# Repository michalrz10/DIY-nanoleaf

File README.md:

# DIY nanoleaf
## Programmed functionality
 - Turn on/off leds
 - Turn on/off build in led
 - Single color
 - Random color on each segment every 5 seconds
 - Single random color every 5 seconds
 - Smooth change on each segment color
 - Smooth change of single color
 - Smooth change of pairs of segments
 - Api to control each segment color. For exaplle changing color with music described in <a href="Pythonn App">Python app</a>  

  Blue eye  
     
  Music Api  
    
## Ways to controll
 - Website
 - <a href="Python App">Windows app</a>
 - <a href="Android App">Android app</a>
## Case
All the <a href="3D model">parts</a> were 3D printed with pla and connected with 1 cm spacers.  
 
There is a reflective material glued on the back of the case.  
Cover was printed in 2 layers of translusend pla. Later I glued thin paper to cover so the light was more diffused.  
   
## Electronics
### Used:
 - Esp32 to controll leds
 - 5m RGB Led strip 12V devided in 10 segments for each hexagon
 - 15 N-Mosfets to controll 5 different colors through Esp32
 - Led power suppy
 - Mini 360 DC-DC step-down converter
  
### Diagram

### <a href="Board project">Board</a>

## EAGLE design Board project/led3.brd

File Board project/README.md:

# Board  
Board Diagram  
  
Generated board

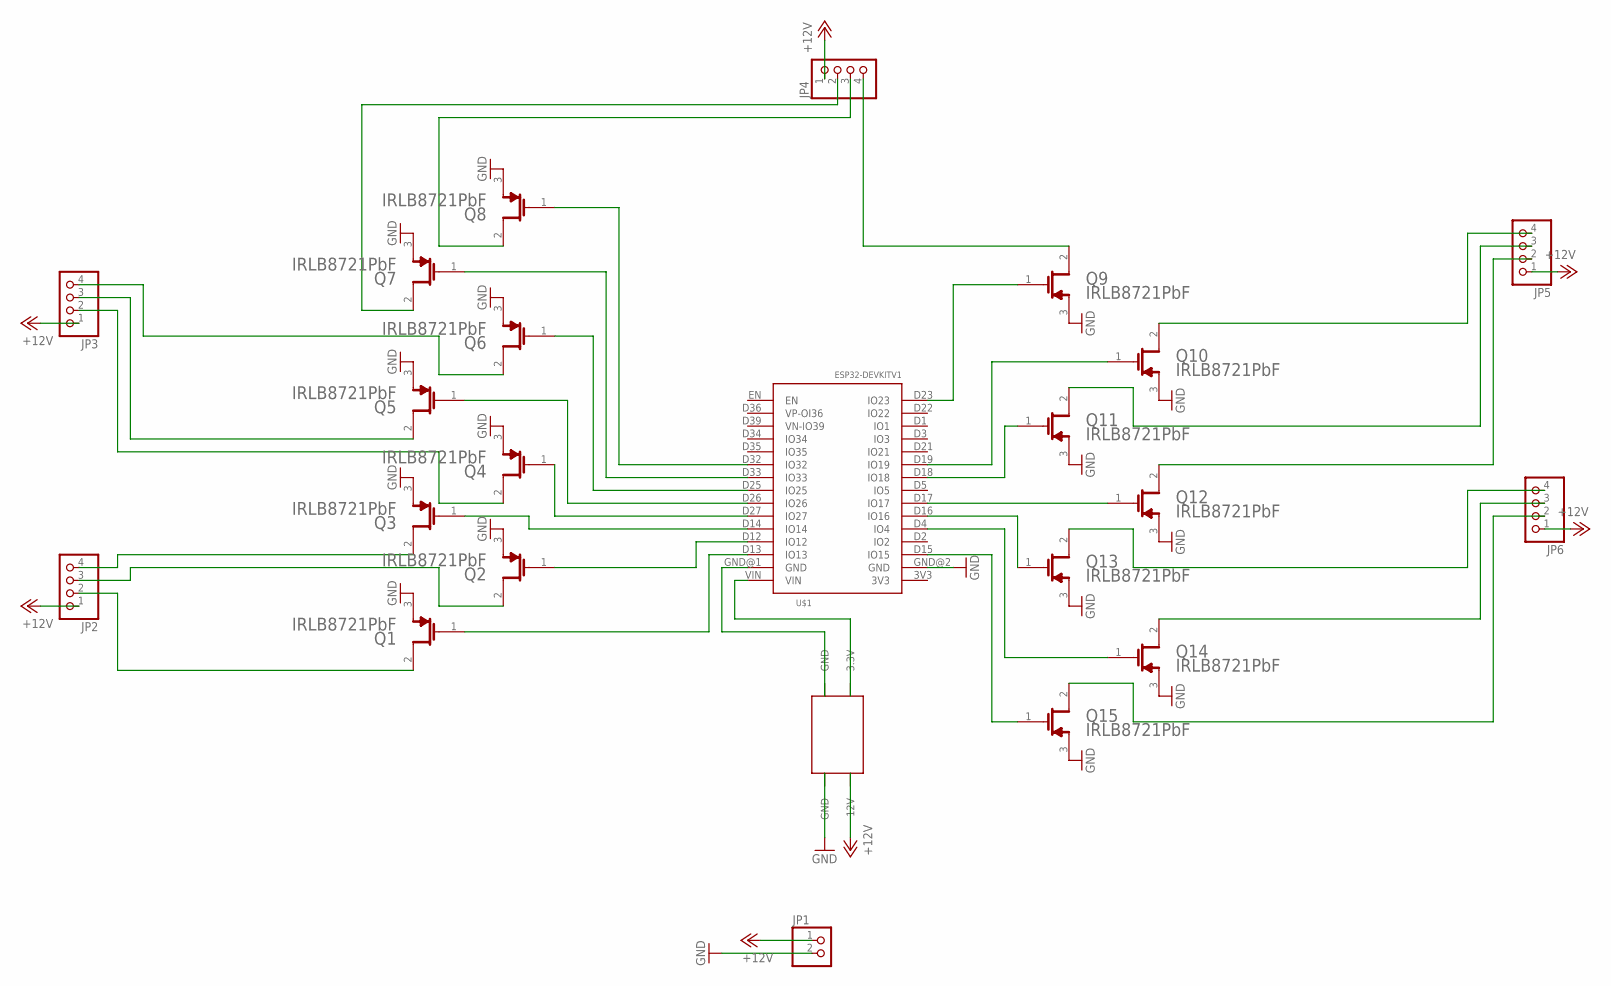
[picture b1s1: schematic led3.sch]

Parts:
JP1: PINHD-1X2; 1X02
JP2, JP3, JP4, JP5, JP6: PINHD-1X4; 1X04
Q1, Q2, Q3, Q4, Q5, Q6, Q7, Q8, Q9, Q10, Q11, Q12, Q13, Q14, Q15: INFINEON_IRLB8721PBFINFINEON_IRLB8721PBF_0_0; INFINEON_IRLB8721PBF_0
U$1: ESP32DEVKITV1; ESP32-DEVKITV1
U$2: MP2307-MINI-360

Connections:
+12V: JP1.1, JP2.1, JP3.1, JP4.1, JP5.1, JP6.1, U$2.12VP (12V)
GND: JP1.2, Q1.3 (S), Q2.3 (S), Q3.3 (S), Q4.3 (S), Q5.3 (S), Q6.3 (S), Q7.3 (S), Q8.3 (S), Q9.3 (S), Q10.3 (S), Q11.3 (S), Q12.3 (S), Q13.3 (S), Q14.3 (S), Q15.3 (S), U$1.GND@2 (GND), U$2.GND@1P (GND)
unnamed: U$1.VIN, U$2.3.3VP (3.3V)
unnamed: Q1.1 (G), U$1.D13 (IO13)
unnamed: Q2.1 (G), U$1.D12 (IO12)
unnamed: Q3.1 (G), U$1.D14 (IO14)
unnamed: JP3.3, Q5.2 (D)
unnamed: JP3.2, Q4.2 (D)
unnamed: Q6.1 (G), U$1.D25 (IO25)
unnamed: Q7.1 (G), U$1.D33 (IO33)
unnamed: Q8.1 (G), U$1.D32 (IO32)
unnamed: Q9.1 (G), U$1.D23 (IO23)
unnamed: Q15.1 (G), U$1.D15 (IO15)
unnamed: Q14.1 (G), U$1.D4 (IO4)
unnamed: Q13.1 (G), U$1.D16 (IO16)
unnamed: Q12.1 (G), U$1.D17 (IO17)
unnamed: Q11.1 (G), U$1.D18 (IO18)
unnamed: Q10.1 (G), U$1.D19 (IO19)
unnamed: JP2.2, Q1.2 (D)
unnamed: JP2.3, Q2.2 (D)
unnamed: JP2.4, Q3.2 (D)
unnamed: Q4.1 (G), U$1.D27 (IO27)
unnamed: Q5.1 (G), U$1.D26 (IO26)
unnamed: JP3.4, Q6.2 (D)
unnamed: JP4.2, Q7.2 (D)
unnamed: JP4.3, Q8.2 (D)
unnamed: JP4.4, Q9.2 (D)
unnamed: JP6.2, Q15.2 (D)
unnamed: JP6.3, Q14.2 (D)
unnamed: JP6.4, Q13.2 (D)
unnamed: JP5.2, Q12.2 (D)
unnamed: JP5.3, Q11.2 (D)
unnamed: JP5.4, Q10.2 (D)
unnamed: U$1.GND@1 (GND), U$2.GND@2P (GND)

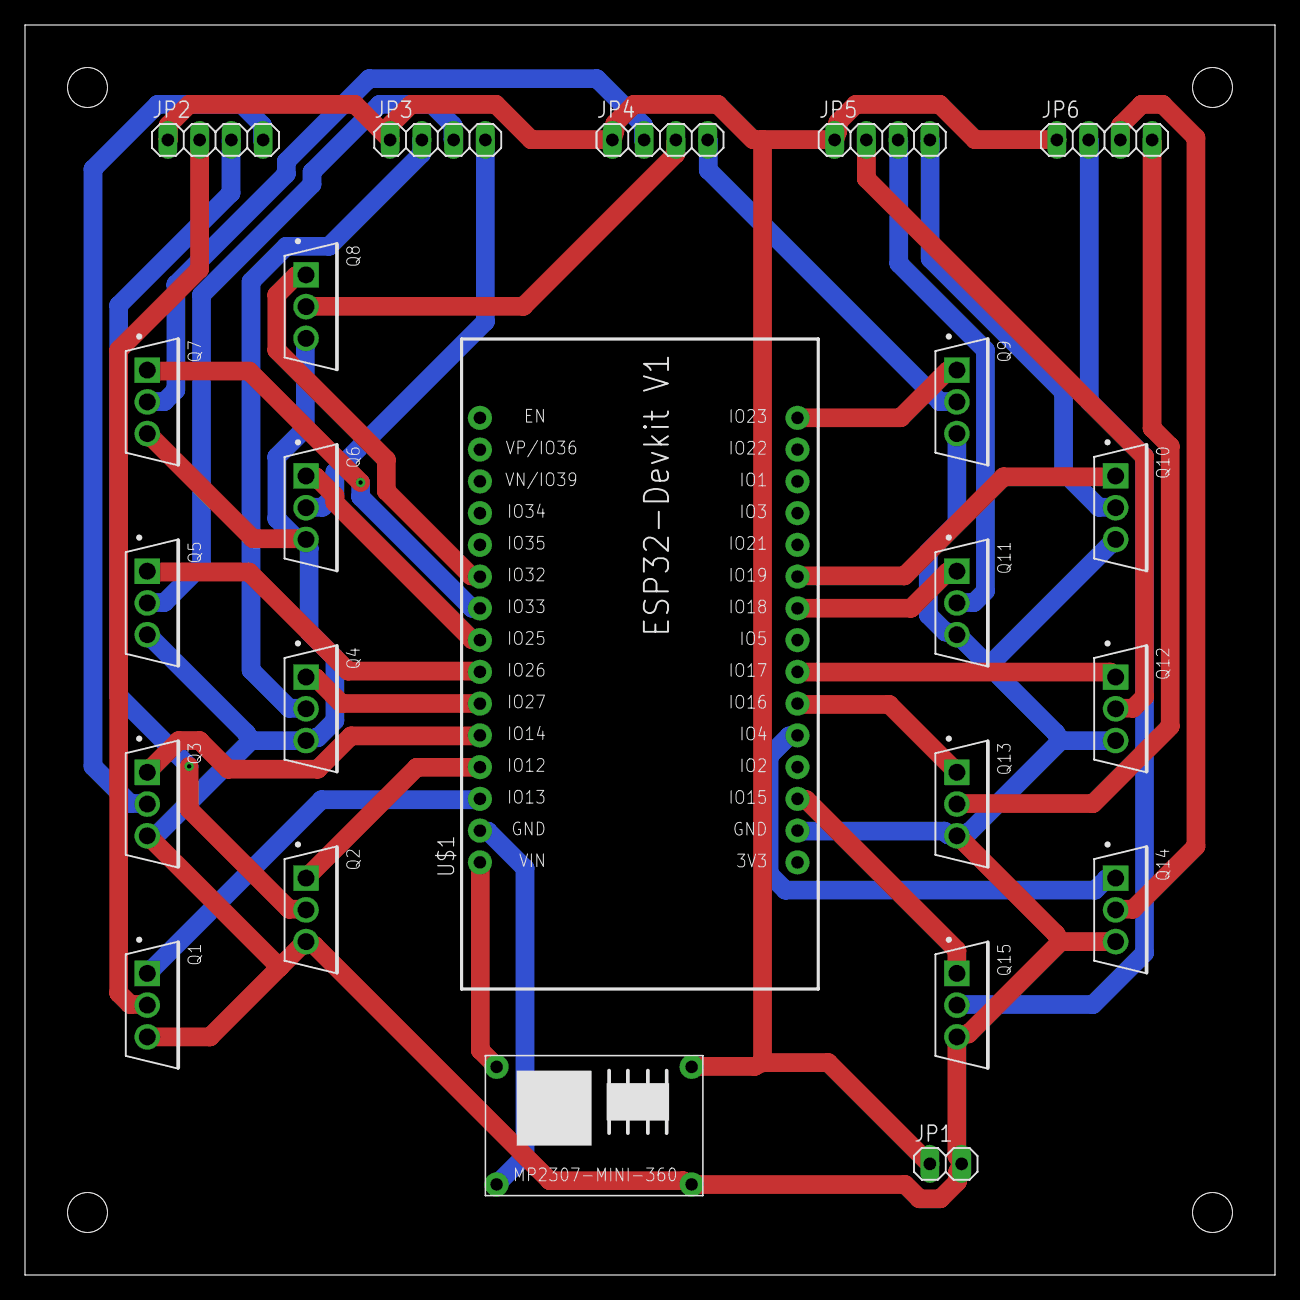
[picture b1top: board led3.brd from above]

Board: 2 copper layers, 100.0 x 100.0 mm, 23 parts (0 on the bottom side), 34 nets.

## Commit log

2022-06-20 3Dmodels
2022-06-20 Board
2022-06-30 Initv2
